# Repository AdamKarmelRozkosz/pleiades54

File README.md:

# Pleiades54
  
### A split mechanical keyboard designed and built by [me](https://github.com/AdamKarmelRozkosz)  
This keyboard features double Atmega 32u4 microprocessors as well as Vial support.  
note* this is first version and it will be further imrpoved with future designs.  

## Requirements 
### Parts 
| Part name | Quantity | link |
|----------------|-----|------------| 
| Atmega 32u4 | 2 | [aliexpress](https://pl.aliexpress.com/item/1005004782408708.html?dp=6914f10dc7fc160512591b8a&cn=ah&aff_fcid=eee0c94e7a554dbb9003fa6172967f3c-1768840323412-05495-_d6jWDbY&aff_fsk=_d6jWDbY&aff_platform=link-c-tool&sk=_d6jWDbY&aff_trace_key=eee0c94e7a554dbb9003fa6172967f3c-1768840323412-05495-_d6jWDbY&terminal_id=4cb5ad5188764f539724dc31512667a9&afSmartRedirect=y) |
| 4 pin buttons | 2 | [aliexpress](https://pl.aliexpress.com/item/1005004067514307.html?spm=a2g0o.order_list.order_list_main.37.7a171c242sNorV&gatewayAdapt=glo2pol) | 
| TRRS ports | 2 | [aliexpress](https://pl.aliexpress.com/item/1005003111662179.html?spm=a2g0o.order_list.order_list_main.57.7a171c242sNorV&gatewayAdapt=glo2pol) | 
| Diodes | 54 | [aliexpress](https://pl.aliexpress.com/item/1005004962400215.html?spm=a2g0o.order_list.order_list_main.42.7a171c242sNorV&gatewayAdapt=glo2pol) |
| Switches | 54 | [unikeys](https://unikeyboards.com/collections/keyboard-switches) |
| Keycaps | 54 | [aliexpress](https://pl.aliexpress.com/item/32842379355.html?spm=a2g0o.order_list.order_list_main.6.3ec51c24qmmrAR&gatewayAdapt=glo2pol) |
| Dual TRRS cable | 1 | [aliexpress](https://pl.aliexpress.com/item/1005008831823377.html?spm=a2g0o.order_list.order_list_main.47.3ec51c24qmmrAR&gatewayAdapt=glo2pol) |  

Switches used in this build were CIY Asura. Any 3 pin switch would be good but when soldering the board I realized that some 5 pin switches won't fit.  
As for keycaps I recommend DSA keycaps just because of the flat profile.
### Software
To compile the software you need to install qmk fork vial-qmk
```
git clone https://github.com/vial-kb/vial-qmk.git
```
## Firmware
To install firmware onto the keyboard please follow these steps.  
#### clone the repo 
```
git clone https://github.com/AdamKarmelRozkosz/pleiades54.git
```
#### First create your keyboard directory
```
cd vail-qmk
```
```
mkdir  keyboards/[name]
```
#### Copy the firmware to the vial-qmk directory
```
cp pleiades54/firmware/pleiades54_REV1 vial-qmk/keyboards/[name]
```
#### Compiling the firmware 
To compile the firmware make sure you are in vial-qmk directory, then you can compile the firmware with this command,
```
make [name]:vial
```
when compiled correctly you should see .hex file 

#### Flashin the firwmare
To flash the firmware onto the keyboard make sure both sides are disconnected from eachother, then plug in one side of the keyboard via usb cable and type this command.
```
make [name]:vial:avrdude-split-left
```
While flashing the firmware it will ask you to reset it, just click twice on the reset button.  
you might want to change left to right depending which side are you flashing first.
then do the same for the other half.
```
make [name]:vial:avrdude-split-right
```
lastly connect them together.  
## Configuration
### Modify keymap.c file
I don't recommend this method but you can directly modify the keymap in this file. Please not that you will have to flash again.
### Vial 
You can use vial configurator as well. This is the *recommended* method. Just visit the [vial](https://vial.rocks/) website or download vial configurator from [here](https://get.vial.today/download/)

## Features
this keyboard features vial support with tap dance enabled from the start and NKRO.

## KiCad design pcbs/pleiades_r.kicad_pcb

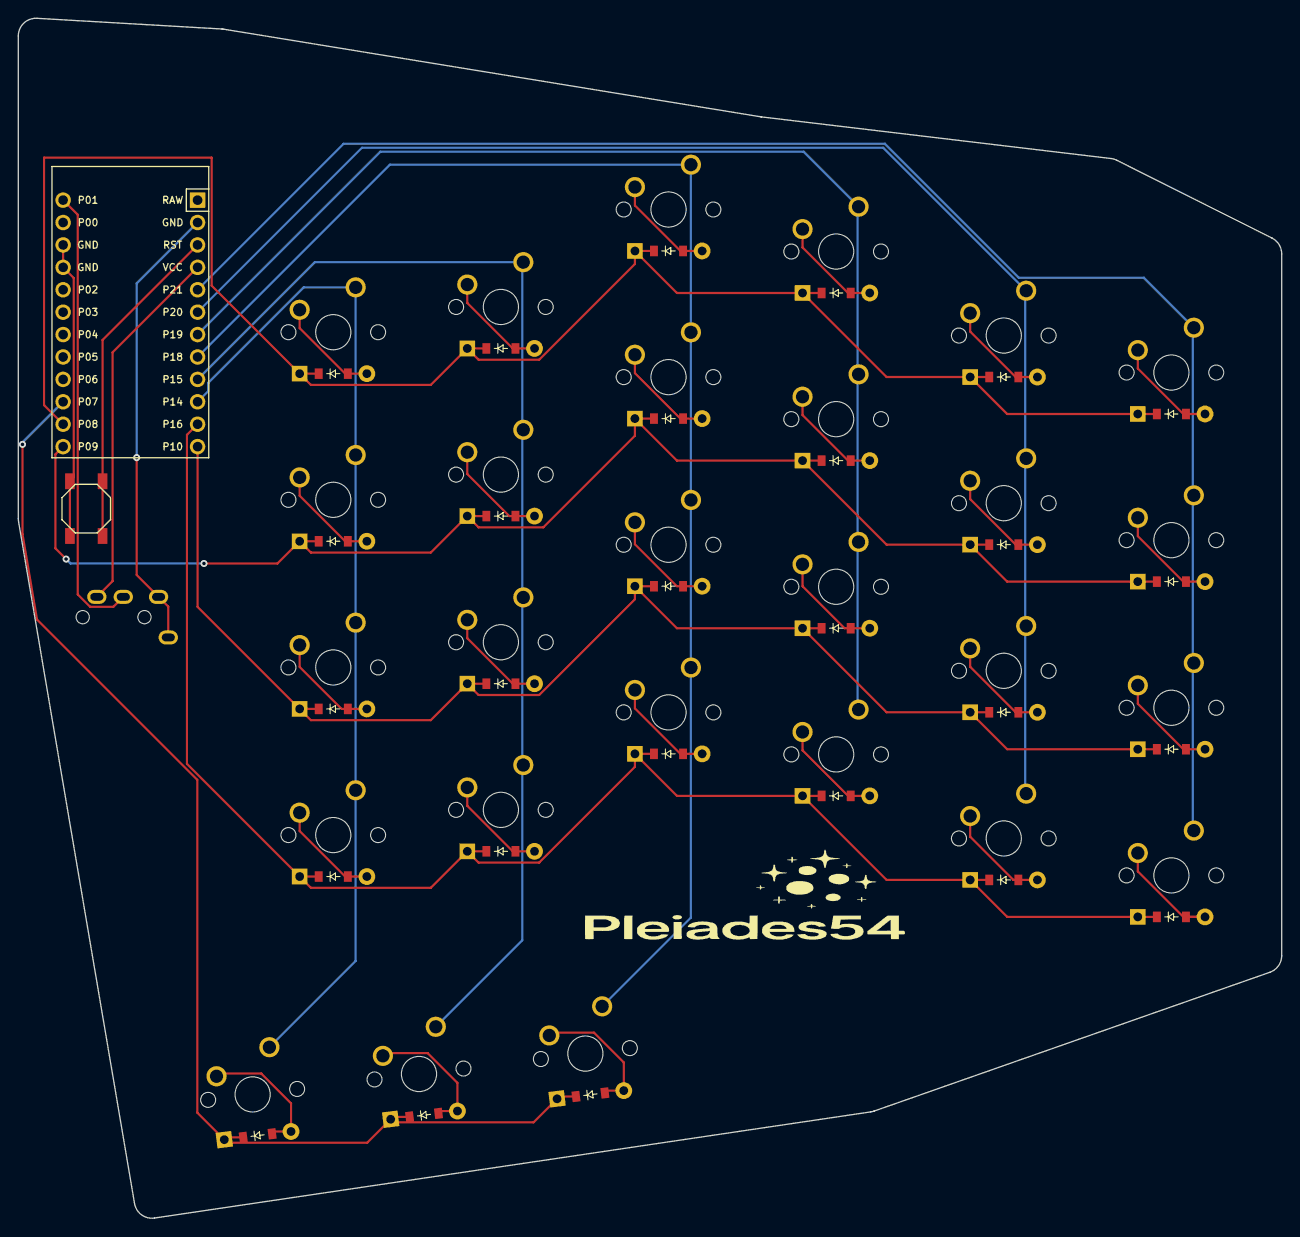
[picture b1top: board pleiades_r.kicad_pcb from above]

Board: 2 copper layers, 143.2 x 136.0 mm, 57 parts (0 on the bottom side), 42 nets.

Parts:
B1: SW_TACT_ALPS_SKQGABE010
D1, D2, D3, D4, D5, D6, D7, D8, D9, D10, D11, D12, D13, D14, D15, D16, D17, D18, D19, D20, D21, D22, D23, D24, D25, D26, D27: ComboDiode
MCU1: ProMicro
S1, S2, S3, S4, S5, S6, S7, S8, S9, S10, S11, S12, S13, S14, S15, S16, S17, S18, S19, S20, S21, S22, S23, S24, S25, S26, S27: MX
TRRS1: TRRS-PJ-320A-dual

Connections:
GND: B1.2, MCU1.2, MCU1.15, MCU1.16, TRRS1.1, TRRS1.2
P1: MCU1.13, TRRS1.3
P7: D25.1, D26.1, D27.1, MCU1.22
P8: D4.1, D8.1, D12.1, D16.1, D20.1, D24.1, MCU1.23
P9: D3.1, D7.1, D11.1, D15.1, D19.1, D23.1, MCU1.24
P10: D2.1, D6.1, D10.1, D14.1, D18.1, D22.1, MCU1.12
P14: MCU1.10, S21.1, S22.1, S23.1, S24.1, S27.1
P15: MCU1.9, S17.1, S18.1, S19.1, S20.1, S26.1
P16: D1.1, D5.1, D9.1, D13.1, D17.1, D21.1, MCU1.11
P18: MCU1.8, S13.1, S14.1, S15.1, S16.1, S25.1
P19: MCU1.7, S9.1, S10.1, S11.1, S12.1
P20: MCU1.6, S5.1, S6.1, S7.1, S8.1
P21: MCU1.5, S1.1, S2.1, S3.1, S4.1
RST: B1.1, MCU1.3
VCC: MCU1.4, TRRS1.4
mirror_alt_main: D25.2, S25.2
mirror_inner_bot: D1.2, S1.2
mirror_inner_mid: D2.2, S2.2
mirror_inner_num: D4.2, S4.2
mirror_inner_top: D3.2, S3.2
mirror_middle_bot: D13.2, S13.2
mirror_middle_mid: D14.2, S14.2
mirror_middle_num: D16.2, S16.2
mirror_middle_top: D15.2, S15.2
mirror_mod_main: D26.2, S26.2
mirror_pinky_bot: D5.2, S5.2
mirror_pinky_mid: D6.2, S6.2
mirror_pinky_num: D8.2, S8.2
mirror_pinky_top: D7.2, S7.2
mirror_point_bot: D17.2, S17.2
mirror_point_mid: D18.2, S18.2
mirror_point_num: D20.2, S20.2
mirror_point_top: D19.2, S19.2
mirror_pointfar_bot: D21.2, S21.2
mirror_pointfar_mid: D22.2, S22.2
mirror_pointfar_num: D24.2, S24.2
mirror_pointfar_top: D23.2, S23.2
mirror_ring_bot: D9.2, S9.2
mirror_ring_mid: D10.2, S10.2
mirror_ring_num: D12.2, S12.2
mirror_ring_top: D11.2, S11.2
mirror_space_main: D27.2, S27.2

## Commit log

2025-05-26 feat: initial pcb setup
2025-06-02 Feat: added gerber files
2025-06-02 Feat: updated pleiades.yaml
2025-11-22 feat: added README file
2026-01-13 fead: added basic firmware for the keyboard with vial nkro vial and tap dance support
2026-01-19 fix: fixed a typo in README
    , instead of .
2026-01-19 feat: added proper README.md file
2026-01-19 fix: Fixed some errors in README.md
2026-01-19 feat: added improved and working firmware to the keyboard
2026-01-19 feat: added photos as well as updared README.md
